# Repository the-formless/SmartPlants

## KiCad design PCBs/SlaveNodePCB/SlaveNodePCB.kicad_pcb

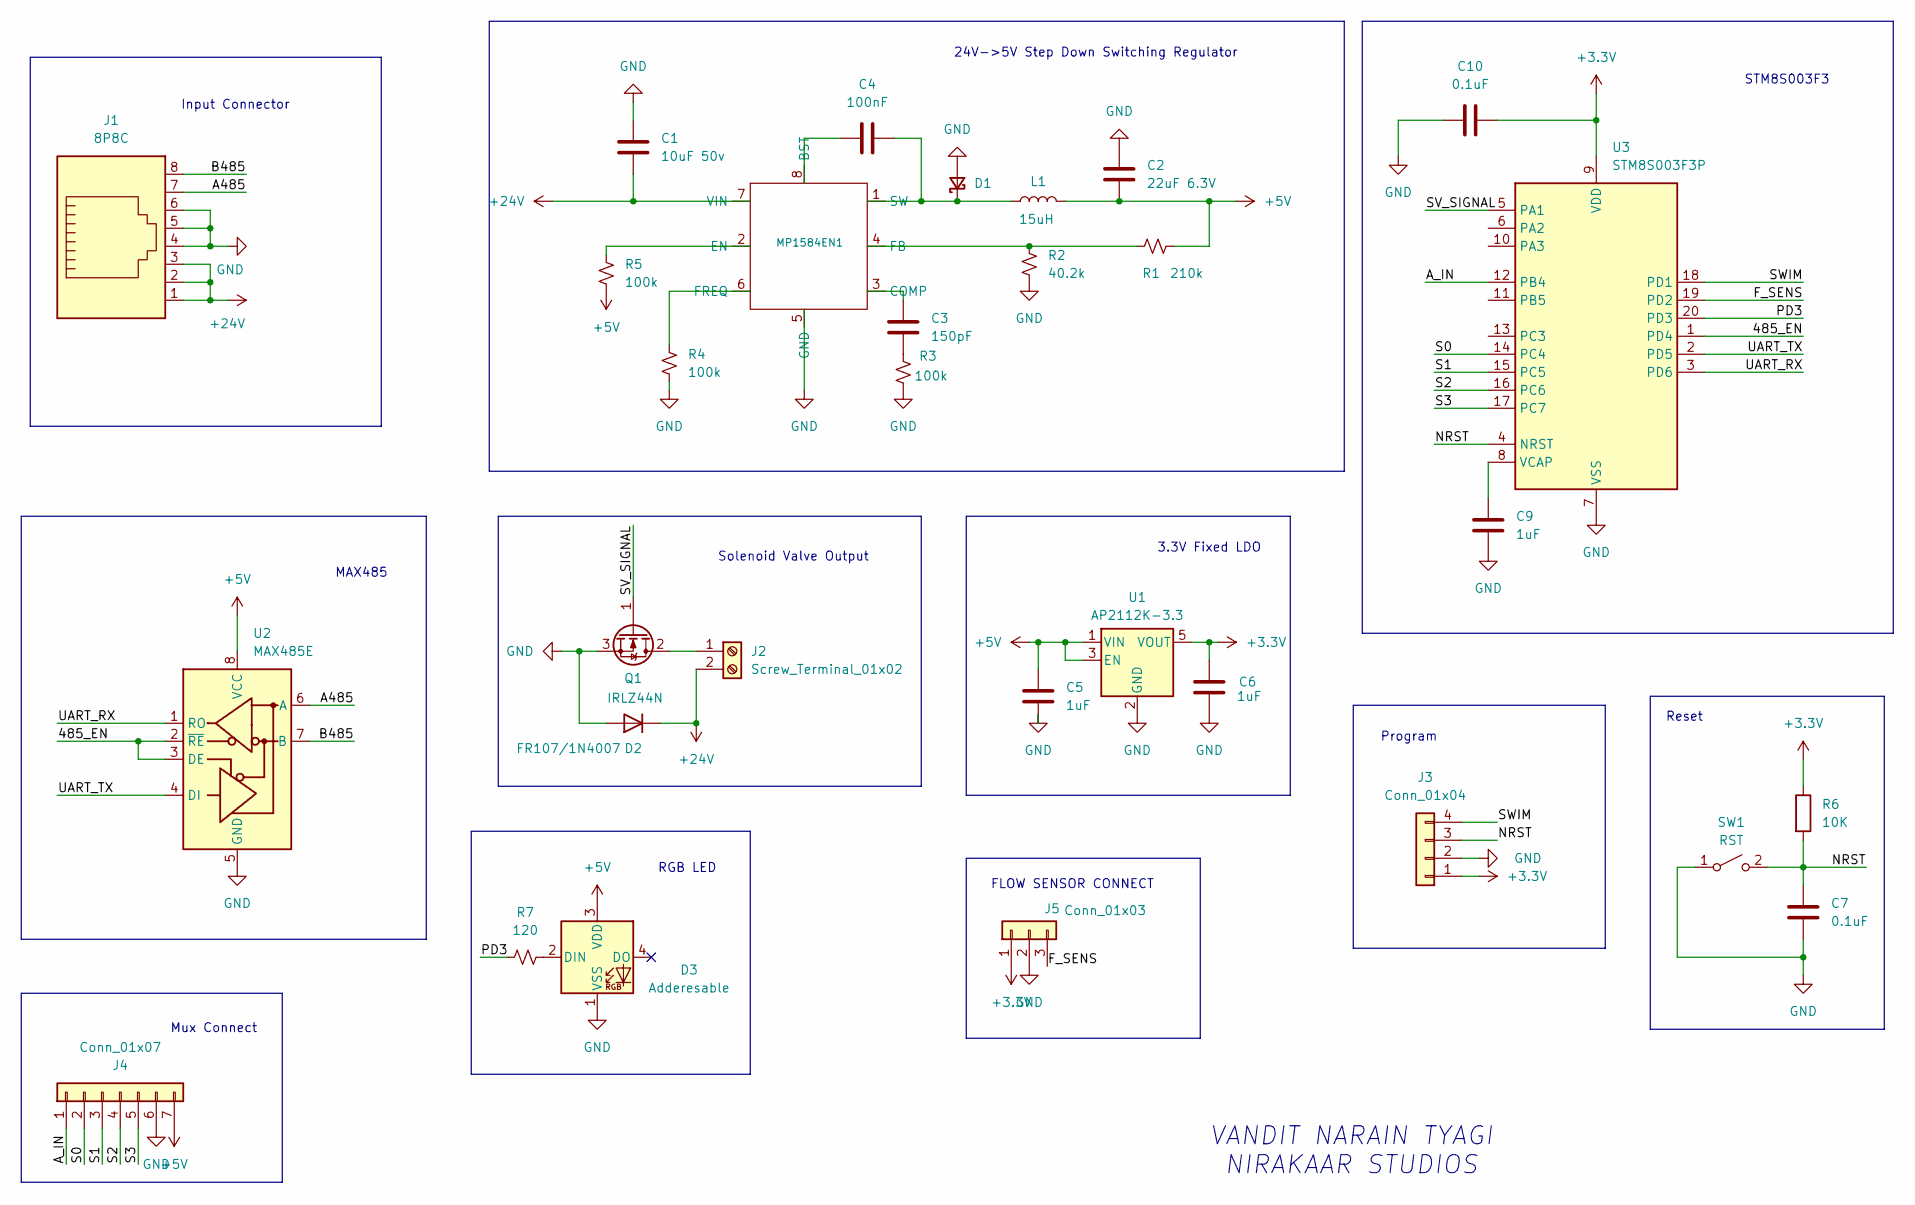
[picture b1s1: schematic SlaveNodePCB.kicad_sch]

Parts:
C1: 10uF 50v; C_0805_2012Metric
C2: 22uF 6.3V; C_0805_2012Metric
C3: 150pF; C_0805_2012Metric
C4: 100nF; C_0805_2012Metric
C5, C6, C9: 1uF; C_0805_2012Metric
C7, C10: 0.1uF; C_0805_2012Metric
D1: D_SMA-SMB_Universal_Handsoldering
D2: FR107/1N4007; D_DO-41_SOD81_P12.70mm_Horizontal
D3: Adderesable; LED_Inolux_IN-PI554FCH_PLCC4_5.0x5.0mm_P3.2mm
J1: 8P8C; RJ45_Ninigi_GE
J2: Screw_Terminal_01x02; TerminalBlock_Phoenix_MKDS-1,5-2-5.08_1x02_P5.08mm_Horizont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
J3: Conn_01x04; PinHeader_1x04_P2.54mm_Vertical
J4: Conn_01x07; PinHeader_1x07_P2.54mm_Vertical
J5: Conn_01x03; PinHeader_1x03_P2.54mm_Vertical
L1: 15uH; L_Changjiang_FNR8040S
MP1584EN1: SO-8_3.9x4.9mm_P1.27mm
Q1: IRLZ44N; TO-220-3_Vertical
R1: 210k; R_0805_2012Metric
R2: 40.2k; R_0805_2012Metric
R3, R4, R5: 100k; R_0805_2012Metric
R6: 10K; R_0805_2012Metric
R7: 120; R_0805_2012Metric
SW1: RST; SW_PUSH_6mm
U1: AP2112K-3.3; SOT-23-5
U2: MAX485E; SOIC-8_3.9x4.9mm_P1.27mm
U3: STM8S003F3P; TSSOP-20_4.4x6.5mm_P0.65mm

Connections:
+3.3V: C6.1, C10.2, J3.1, J5.1, R6.1, U1.5 (VOUT), U3.9 (VDD)
+5V: C2.2, C5.1, D3.3 (VDD), J4.7, L1.2, R1.2, R5.1, U1.1 (VIN), U1.3 (EN), U2.8 (VCC)
+24V: C1.2, D2.1 (K), J1.1, J1.2, J1.3, J2.2, MP1584EN1.7 (VIN)
/485_EN: U2.2 (~RE), U2.3 (DE), U3.1 (PD4)
/A485: J1.7, U2.6 (A)
/A_IN: J4.1, U3.12 (PB4)
/B485: J1.8, U2.7 (B)
/F_SENS: J5.3, U3.19 (PD2)
/NRST: C7.1, J3.3, R6.2, SW1.2 (B), U3.4 (NRST)
/PD3: R7.1, U3.20 (PD3)
/S0: J4.2, U3.14 (PC4)
/S1: J4.3, U3.15 (PC5)
/S2: J4.4, U3.16 (PC6)
/S3: J4.5, U3.17 (PC7)
/SV_SIGNAL: Q1.1 (G), U3.5 (PA1)
/SWIM: J3.4, U3.18 (PD1)
/UART_RX: U2.1 (RO), U3.3 (PD6)
/UART_TX: U2.4 (DI), U3.2 (PD5)
GND: C1.1, C2.1, C5.2, C6.2, C7.2, C9.2, C10.1, D1.2 (A), D2.2 (A), D3.1 (VSS), J1.4, J1.5, J1.6, J3.2, J4.6, J5.2, MP1584EN1.5 (GND), Q1.3 (S), R2.2, R3.1, R4.2, SW1.1 (A), U1.2 (GND), U2.5 (GND), U3.7 (VSS)
unnamed: C3.2, R3.2
unnamed: C4.2, D1.1 (K), L1.1, MP1584EN1.1 (SW)
unnamed: D3.2 (DIN), R7.2
unnamed: J2.1, Q1.2 (D)
unnamed: C4.1, MP1584EN1.8 (BST)
unnamed: C3.1, MP1584EN1.3 (COMP)
unnamed: MP1584EN1.2 (EN), R5.2
unnamed: MP1584EN1.4 (FB), R1.1, R2.1
unnamed: MP1584EN1.6 (FREQ), R4.1
unnamed: C9.1, U3.8 (VCAP)

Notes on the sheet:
24V->5V Step Down Switching Regulator
Mux Connect
Program
MAX485
Reset
Solenoid Valve Output
Input Connector
VANDIT NARAIN TYAGI NIRAKAAR STUDIOS
RGB LED
FLOW SENSOR CONNECT
STM8S003F3
3.3V Fixed LDO

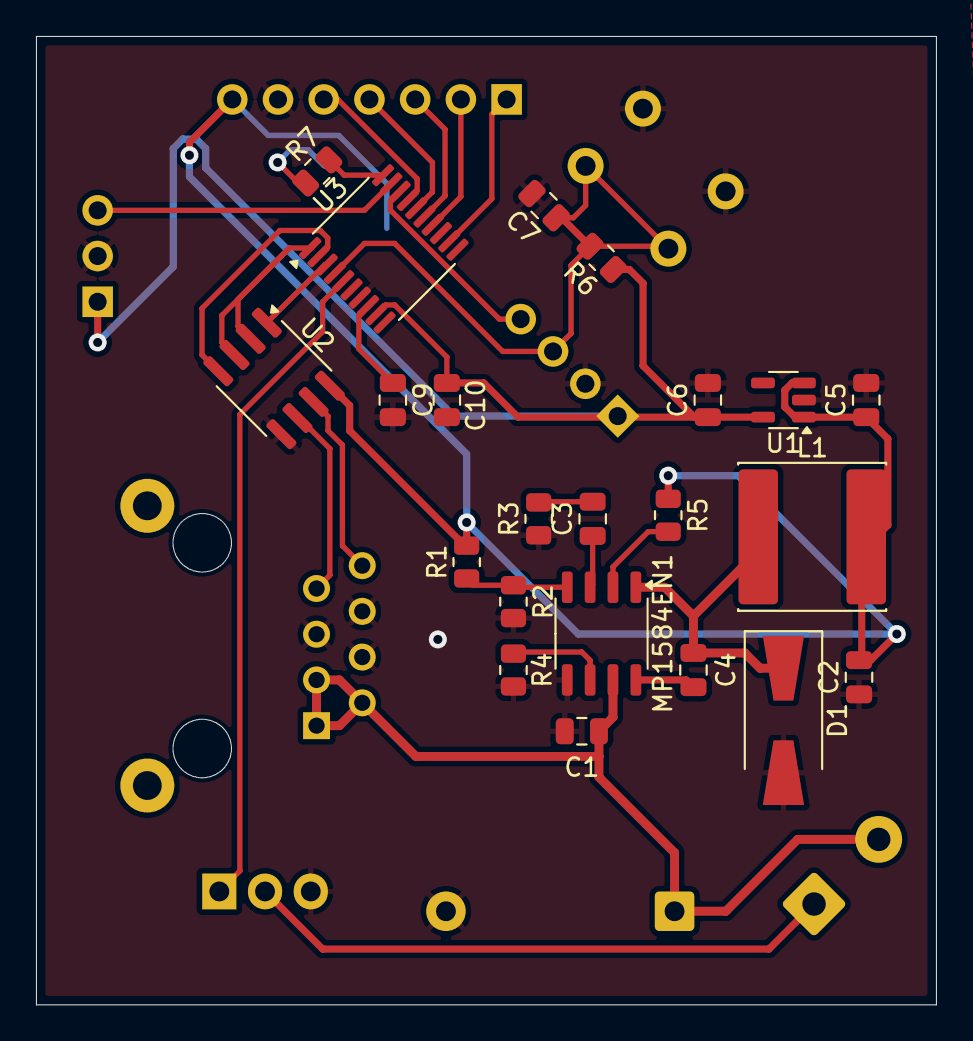
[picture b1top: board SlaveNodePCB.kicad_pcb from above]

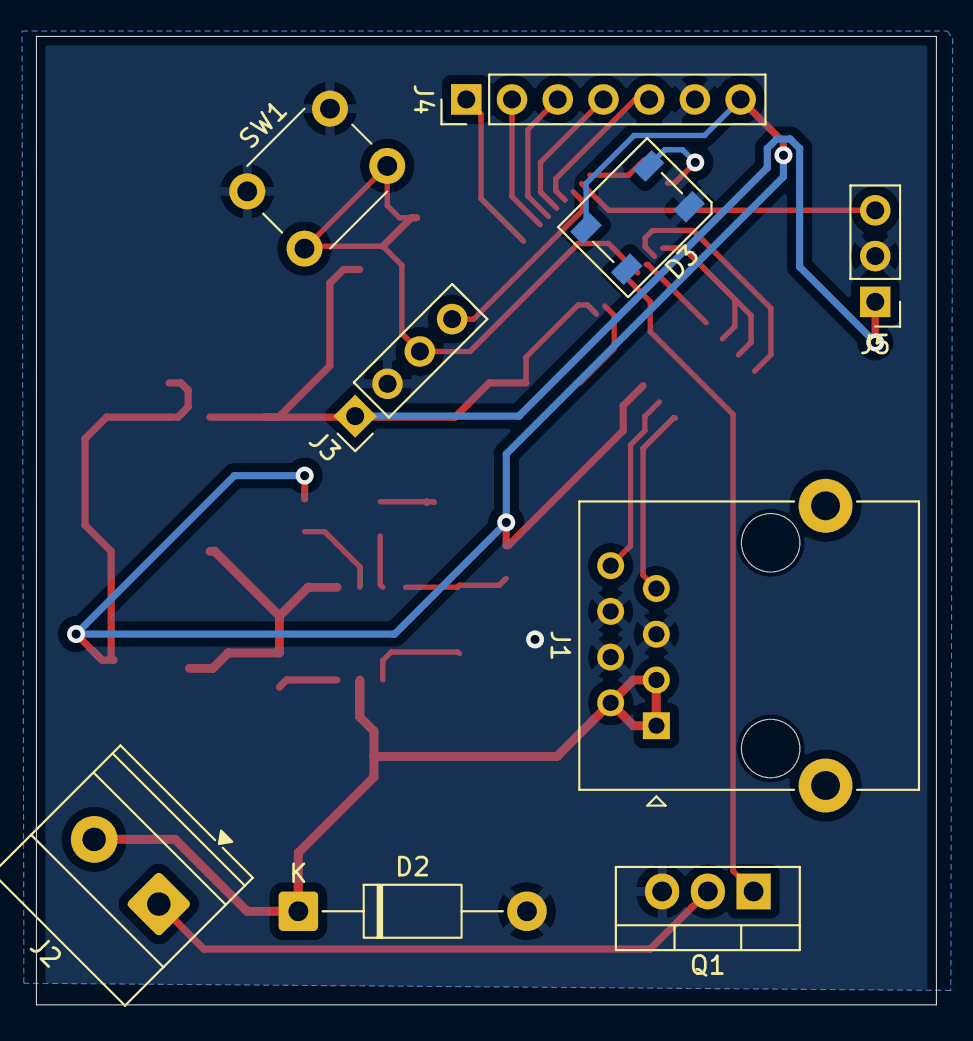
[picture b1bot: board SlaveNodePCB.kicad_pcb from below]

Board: 2 copper layers, 50.0 x 53.8 mm, 31 parts (9 on the bottom side), 29 nets.

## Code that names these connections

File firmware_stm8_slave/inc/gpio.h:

#ifndef STM8_GPIO_H
#define STM8_GPIO_H

#include <stdint.h> 

//GPIO Register STruct

typedef struct
{
  volatile uint8_t ODR;   // Output Data Register
  volatile uint8_t IDR;   // Input Data Register
  volatile uint8_t DDR;   // Data Direction Register
  volatile uint8_t CR1;   // Control Register 1
  volatile uint8_t CR2;   // Control Register 2
} GPIO_Port;

//--
//Base Addresses
//--
#define GPIOA ((volatile GPIO_Port*) 0x5000)
#define GPIOB ((volatile GPIO_Port*) 0x5005)
#define GPIOC ((volatile GPIO_Port*) 0x500A)
#define GPIOD ((volatile GPIO_Port*) 0x500F)
#define GPIOE ((volatile GPIO_Port*) 0x5014)
#define GPIOF ((volatile GPIO_Port*) 0x5019) 

//helper macros
#define GPIO_PIN(n) (1 << (n))

//HAL Enums
typedef enum {
    GPIO_MODE_INPUT = 0,
    GPIO_MODE_OUTPUT = 1
} GPIO_Mode;

typedef enum {
    GPIO_NOPULL = 0,
    GPIO_PULLUP = 1
} GPIO_Pull;

typedef enum {
    GPIO_OUTPUT_PUSHPULL = 0,
    GPIO_OUTPUT_OPENDRAIN = 1
} GPIO_OutputType;

typedef enum {
    GPIO_SPEED_SLOW = 0,
    GPIO_SPEED_FAST = 1 
} GPIO_Speed;

//-----
//GPIO Initialization Config
//-----
typedef struct {
    // uint8_t pin;    //defining PINs separately for better readability
    GPIO_Mode mode;
    GPIO_Pull pull;
    GPIO_OutputType outputType; // Only relevant if mode is OUTPUT
    GPIO_Speed speed;           // Only relevant if mode is OUTPUT
} GPIO_InitTypeDef;


typedef struct {
    volatile GPIO_Port *port;
    uint8_t pin;
} GPIO_Pin;

//-----
//GPIO Pin defs
//-----
#define PA1 ((GPIO_Pin){GPIOA, 1})
#define PA2 ((GPIO_Pin){GPIOA, 2})
#define PA3 ((GPIO_Pin){GPIOA, 3})
#define PB4 ((GPIO_Pin){GPIOB, 4})
#define PB5 ((GPIO_Pin){GPIOB, 5})
#define PC3 ((GPIO_Pin){GPIOC, 3})
#define PC4 ((GPIO_Pin){GPIOC, 4})
#define PC5 ((GPIO_Pin){GPIOC, 5})
#define PC6 ((GPIO_Pin){GPIOC, 6})
#define PC7 ((GPIO_Pin){GPIOC, 7})
#define PD3 ((GPIO_Pin){GPIOD, 3})
#define PD2 ((GPIO_Pin){GPIOD, 2})
#define PD4 ((GPIO_Pin){GPIOD, 4})
#define PD5 ((GPIO_Pin){GPIOD, 5})
#define PD6 ((GPIO_Pin){GPIOD, 6})

// added macros for True Open Drain pin checking 
#define IS_TRUE_OPEN_DRAIN_PIN(port, pin) \
    ((port == GPIOB) && ((pin == 4) || (pin == 5)))


//-----
//GPIO HAL Functions
//-----
void GPIO_InitPin(volatile GPIO_Pin pin, GPIO_InitTypeDef *config);
// void GPIO_WritePin(volatile GPIO_Port * port, uint8_t pin, uint8_t value);
// uint8_t GPIO_ReadPin(volatile GPIO_Port * port, uint8_t pin);
// void GPIO_TogglePin(volatile GPIO_Port * port, uint8_t pin);
void GPIO_WritePin(volatile GPIO_Pin pin, uint8_t value);
uint8_t GPIO_ReadPin(volatile GPIO_Pin pin);
void GPIO_TogglePin(volatile GPIO_Pin pin);

void GPIO_WritePort(volatile GPIO_Port * port, uint8_t value);
uint8_t GPIO_ReadPort(volatile GPIO_Port * port);   
void GPIO_SetPinMode(GPIO_Pin pin, GPIO_Mode mode);
void GPIO_SetPinAF(GPIO_Pin pin);
void GPIO_I2C_ReleaseBus(GPIO_Pin scl, GPIO_Pin sda);


#endif

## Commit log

2025-11-17 Initialize
2025-11-26 LED Blink Test with custom HAL
2025-11-26 Changed register offset values
2025-11-26 added DDR setting
2025-11-26 fixed GPIO mode definitions and in gpio hal.h and fixed implementation in led.c
2025-11-26 Test from GPT code
2025-11-26 Makefile added
2025-11-26 changed delay value
2025-11-27 Fresh structured GPIO headers
2025-11-27 Completed and tested GPIO HAL
2025-11-27 Added checks for True Open Drain Ports and forced Correct Initialization
2025-11-27 Added Tim4 implementation and delay function
2025-11-28 Implemented UART and tested with arduino. TX works. RX not working properly
2025-11-28 It sends and read. Read is limited to only 1 character. Interrupts will solve this
2025-11-28 ISR works and can now send and receive data from arduino
2025-11-28 Implemented Ring Buffer
2025-11-28 TX interrup non block implemented
2025-11-28 TIM2 Gated TX implemented
2025-11-28 Semi-Working WS2812 protocol. can possibly be fixed by signal level shifting
2025-11-28 Wrote basic packet structure and parsin. Testing needs I2C OLED. will develop I2C Hal first
2025-11-28 program hanging. Need ot check back with main branch
2025-11-29 fresh i2c skeleton
2025-11-29 Stash commit
2025-11-29 functioning basic i2c layer
2025-11-29 Working i2c through lcd. lcd needs FSM to avoid clashes with interrupts and main loop
2025-11-30 Stash commit to fix i2c
2025-11-30 Stash 2
2025-11-30 stash again
2025-11-30 removed uart tim2 interrupt handle
2025-12-01 i2c fsm and lcd fsm code
2025-12-01 Task scheduler implemented with UART and heartbeat tasks functioning
2025-12-02 Added PCB directory and Slave PCB project
2025-12-03 Designed Slave PCB schematic
2025-12-05 First Slave PCB Design Complete
2025-12-17 Current Slave PCB
